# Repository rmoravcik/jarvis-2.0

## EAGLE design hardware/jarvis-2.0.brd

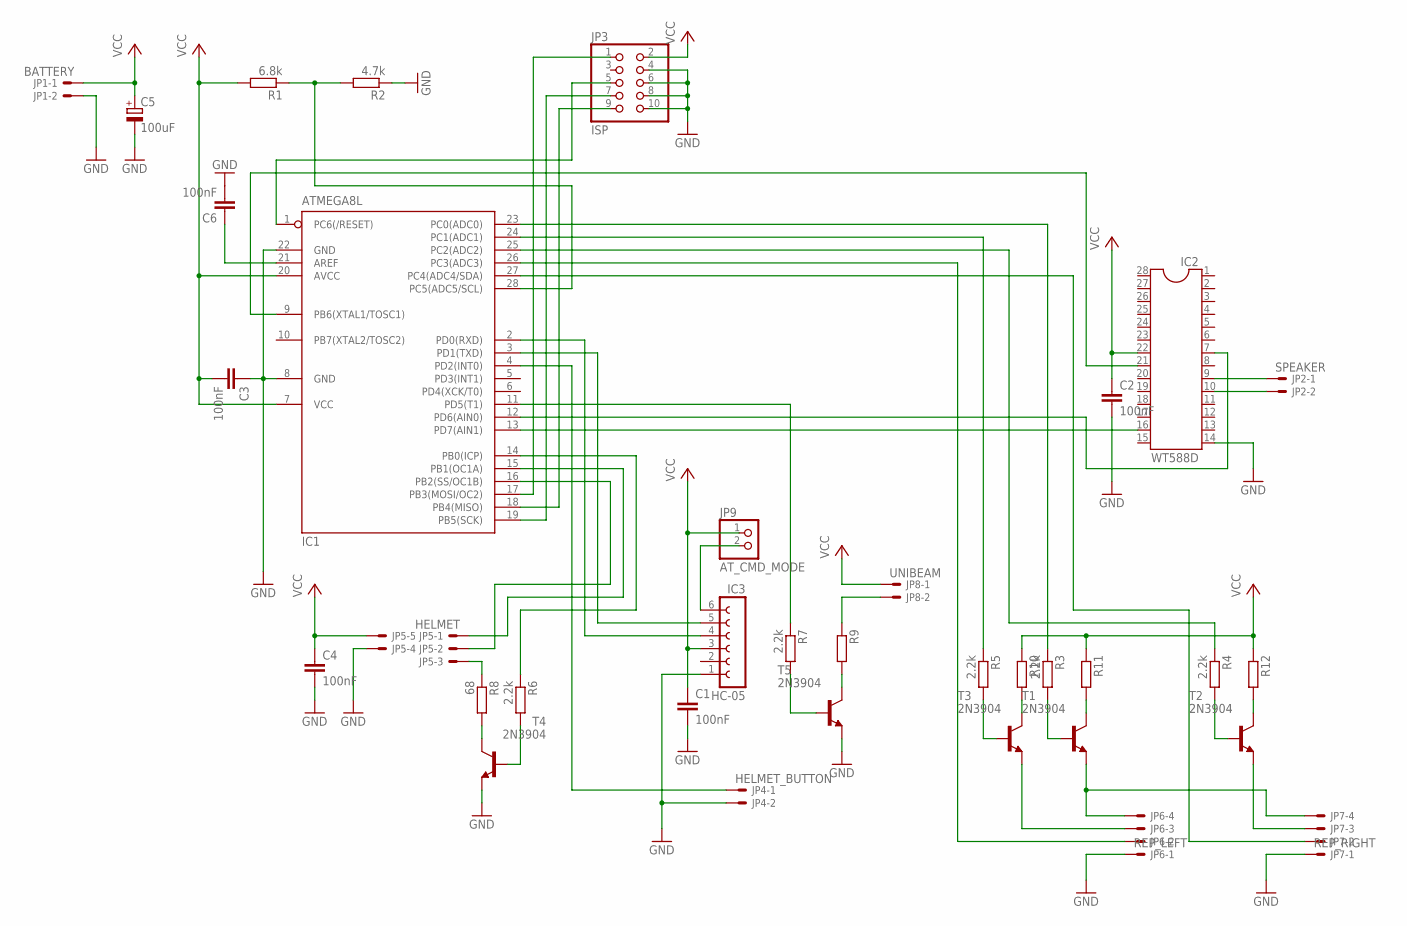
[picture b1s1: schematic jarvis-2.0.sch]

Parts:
C1, C2, C3, C4, C6: 100nF; C2.5-2
C5: 100uF; E5-5
IC1: ATMEGA8L; DIL28-3
IC2: WT588D; DIL28-6
IC3: HC-05; FE06
JP1: BATTERY; 22-23-2021
JP2: SPEAKER; 22-23-2021
JP3: ISP; 2X05
JP4: HELMET_BUTTON; 22-23-2021
JP5: HELMET; 22-23-2051
JP6: REP_LEFT; 22-23-2041
JP7: REP_RIGHT; 22-23-2041
JP8: UNIBEAM; 22-23-2021
JP9: AT_CMD_MODE; 1X02
R1: 6.8k; 0204/7
R2: 4.7k; 0204/7
R3, R4, R5, R6, R7: 2.2k; 0204/7
R8: 68; 0204/7
R9, R10, R11, R12: R-EU_0204/7; 0204/7
T1, T2, T3, T4, T5: 2N3904; TO92-CBE

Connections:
B$1: IC1.14 (PB0(ICP)), R6.1
GND: C1.2, C2.2, C3.1, C4.2, C5.-, C6.2, IC1.8 (GND), IC1.22 (GND), IC2.14, IC3.1, JP1.2, JP3.4, JP3.6, JP3.8, JP3.10, JP4.2, JP5.4, JP6.1, JP7.1, R2.1, T4.E, T5.E
unnamed: IC1.3 (PD1(TXD)), IC3.5
unnamed: IC1.2 (PD0(RXD)), IC3.4
unnamed: IC1.4 (PD2(INT0)), JP4.1
unnamed: IC1.28 (PC5(ADC5/SCL)), R1.1, R2.2
unnamed: IC2.9, JP2.1
unnamed: IC2.10, JP2.2
unnamed: IC1.13 (PD7(AIN1)), IC2.16
unnamed: IC1.9 (PB6(XTAL1/TOSC1)), IC2.21
unnamed: IC1.17 (PB3(MOSI/OC2)), JP3.1
unnamed: IC1.18 (PB4(MISO)), JP3.9
unnamed: IC1.19 (PB5(SCK)), JP3.7
unnamed: IC1.16 (PB2(SS/OC1B)), JP5.2
unnamed: IC1.15 (PB1(OC1A)), JP5.1
unnamed: IC1.11 (PD5(T1)), R7.1
unnamed: IC1.23 (PC0(ADC0)), R3.1
unnamed: R6.2, T4.B
unnamed: JP8.2, R9.1
unnamed: R3.2, T1.B
unnamed: R7.2, T5.B
unnamed: R4.2, T2.B
unnamed: IC1.12 (PD6(AIN0)), IC2.7
unnamed: IC1.24 (PC1(ADC1)), R5.1
unnamed: R5.2, T3.B
unnamed: IC1.25 (PC2(ADC2)), R4.1
unnamed: JP6.4, JP7.4, T1.E
unnamed: JP6.3, T3.E
unnamed: JP7.3, T2.E
unnamed: IC1.26 (PC3(ADC3)), JP6.2
unnamed: IC1.27 (PC4(ADC4/SDA)), JP7.2
unnamed: JP5.3, R8.1
unnamed: R8.2, T4.C
unnamed: R9.2, T5.C
unnamed: R12.2, T2.C
unnamed: R11.2, T1.C
unnamed: R10.2, T3.C
unnamed: C6.1, IC1.21 (AREF)
unnamed: IC3.6, JP9.2
unnamed: IC1.1 (PC6(/RESET)), JP3.5
VCC: C1.1, C2.1, C3.2, C4.1, C5.+, IC1.7 (VCC), IC1.20 (AVCC), IC2.22, IC3.3, JP1.1, JP3.2, JP5.5, JP8.1, JP9.1, R1.2, R10.1, R11.1, R12.1

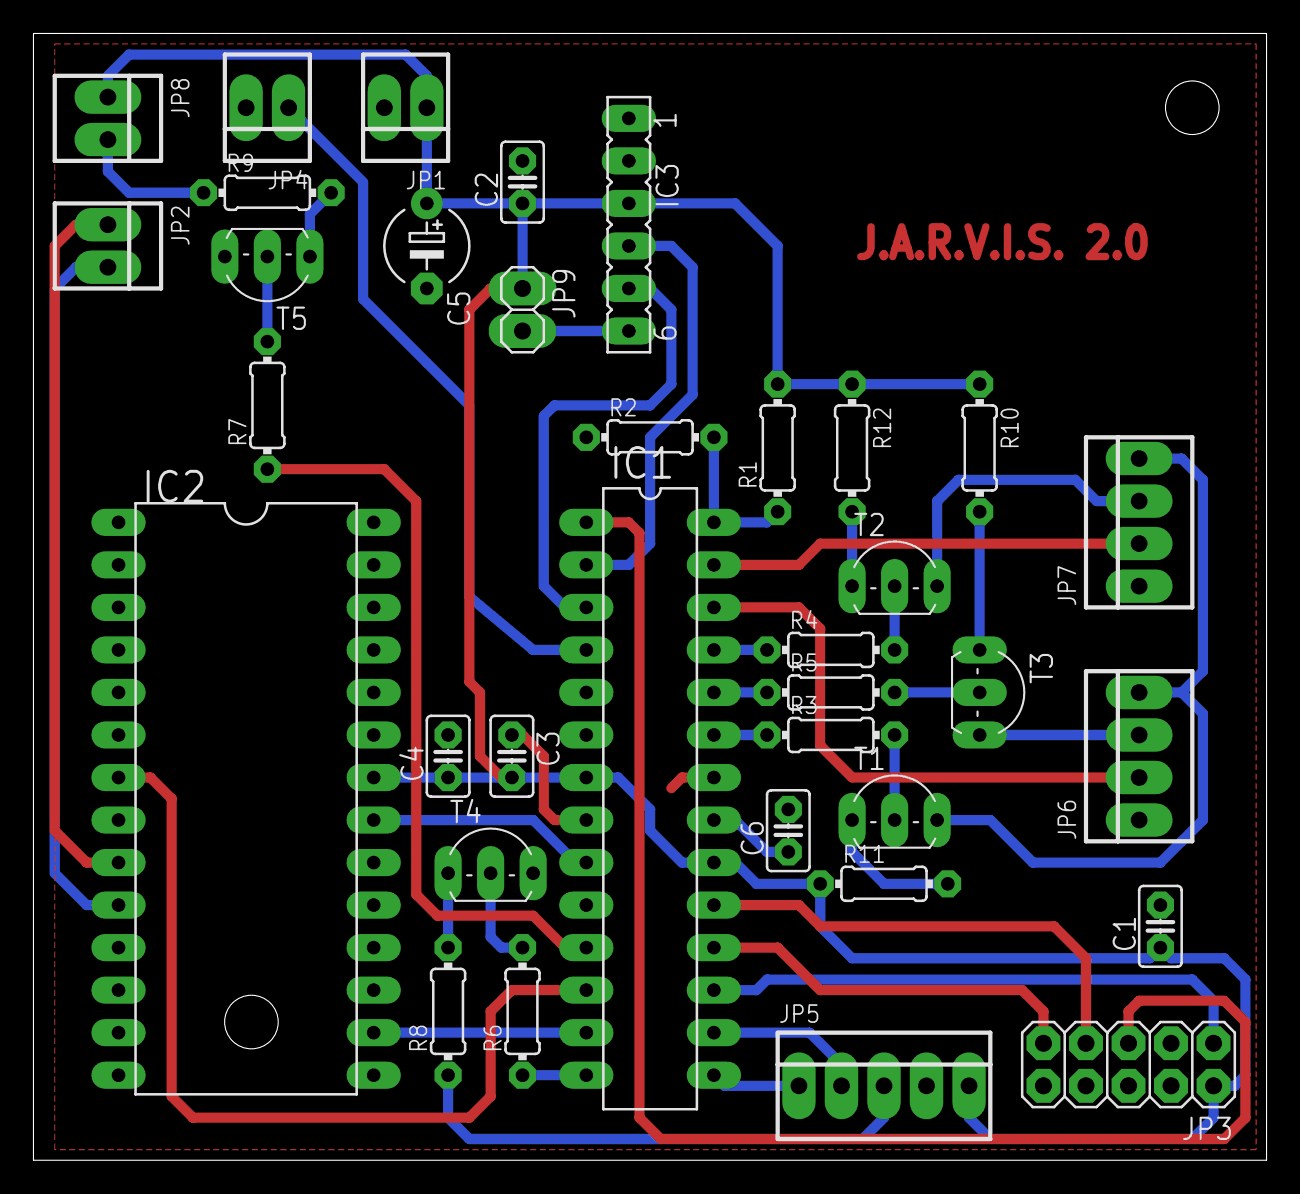
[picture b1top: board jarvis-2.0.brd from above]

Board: 2 copper layers, 73.6 x 67.3 mm, 35 parts (0 on the bottom side), 41 nets.

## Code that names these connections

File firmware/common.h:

/*
 *  jarvis-2.0
 *  Copyright (C) 2014 Roman Moravcik
 *
 *  This program is free software; you can redistribute it and/or modify
 *  it under the terms of the GNU General Public License as published by
 *  the Free Software Foundation; either version 2 of the License, or
 *  (at your option) any later version.
 *
 *  This program is distributed in the hope that it will be useful,
 *  but WITHOUT ANY WARRANTY; without even the implied warranty of
 *  MERCHANTABILITY or FITNESS FOR A PARTICULAR PURPOSE.  See the
 *  GNU General Public License for more details.
 *
 *  You should have received a copy of the GNU General Public License
 *  along with this program; if not, write to the Free Software
 *  Foundation, Inc., 59 Temple Place, Suite 330, Boston, MA  02111-1307  USA
 */

#ifndef COMMON_H
#define COMMON_H

#include <avr/io.h>

#define TRUE				1
#define FALSE				0

#define GPIO_EYES			PB0
#define GPIO_SERVO1			PB1
#define GPIO_SERVO2			PB2
#define GPIO_WT588_BUSY			PB6

#define GPIO_REPULSORS_PWR		PC0
#define GPIO_REPULSOR_LEFT		PC1
#define GPIO_REPULSOR_RIGHT		PC2
#define GPIO_REPULSOR_BUTTON_LEFT	PC3
#define GPIO_REPULSOR_BUTTON_RIGHT	PC4
#define GPIO_BATTERY_SENSE		PC5

#define GPIO_HC05_RXD			PD0
#define GPIO_HC05_TXD			PD1
#define GPIO_FUNC_BUTTON		PD2
#define GPIO_UNIBEAM			PD5
#define GPIO_WT588_RESET		PD6
#define GPIO_WT588_DATA			PD7

#endif // COMMON_H

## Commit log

2014-07-30 Import from iron-man-helmet-controller
2014-07-30 Renamed to jarvis-2.0
2014-07-30 Added wt588d project.
2014-07-30 Removed WT588D Reset pin
2014-07-30 Fixed project name in header
2014-07-30 Code updated to latest HW version.
2014-07-30 Disabled reset
2014-07-31 Tune battery capacity measure
2014-07-31 Changes to follow latest wt588d bin.
2014-08-03 Added ACDC sound
2014-08-03 Added custom random generator
2014-08-04 Fixed random generator. Fixed random generator.#
2014-08-06 Initial bluetooth implementation.
2014-08-06 Added quotes.
2014-08-07 Added comments to code.
2014-08-07 Fixed value of eyes leds resitor.
2014-08-07 Update code to use internal 8Mhz clock.
2014-08-07 Rewritten HC-05 initialization.
2014-08-07 Added hint to get OSCCAL value.
2014-08-07 Added value of OSCCAL register.
2014-08-07 Try to read response.
2014-08-08 Fixed initialization of HC-05.
2014-08-08 Added interrupt driven UART RX.
2014-08-08 Testing receive code
2014-08-10 Fixed serial communucation.
2014-08-10 Cleanup of code.
2014-08-11 Hardcoded strings moved to strings.h
2014-08-11 eyes, repulsor modules replaced by common power module.
2014-08-11 Added command "VERSION"
2014-08-11 Added repulsor button support.
2014-08-11 Print statistics in human readable formtat
2014-08-11 Replace deprecated GIMSK with GICR register.
2014-08-11 Added simple help, unibeam and repulsor commands
2014-08-11 Cleanup of unused sounds.
2014-08-11 Improved blink effect.
2014-08-11 Replace 1 << x with _BV(x) macro.
2014-08-11 Fix compile warning.
2014-08-12 battery_report_capacity() moved to battery.c
2014-08-12 Removed unnecessary code.
2014-08-12 SOUND_CLOCK_AFTERNOON added to voice_play_random()
2014-08-12 Fixed repulsor button logic.
2014-08-13 Added delay before turning on repulsors.
2014-08-13 Handling of repuslor buttons moved to seperated functions.
2014-08-13 Periodic battery checking.
2014-08-13 Allow stoping of playback of random voice messages.
2014-08-13 Report only battery capacity changes.
2014-08-13 Do no ignore report_high flag.
2014-08-14 WT588D busy signal fixes.
2014-08-14 Tabs replaces by spaces. Fixed new line character at the of help.
2014-08-15 Added fortune command. Uppercase serial input.
2014-08-15 Added battery command.
2014-08-15 BUSY fixes 2.
2014-08-15 Revert previous commit.
2014-08-15 BUSY signal fixes 2.
2014-08-15 BUSY fixes 3.
2014-08-18 Added 'REBOOT' command.
2014-08-18 Do not open helmet after reboot if it was closed before.
2014-08-18 Eyes power management moved to helmet module.
2014-08-18 random function moved to voice module.
2014-08-19 Updated sound enum to the latest wt588d firmware.
2014-08-19 Play sound on helmet openning.
2014-08-19 Added playback of new sounds.
2014-08-19 Minize read/write access to internal EEPROM.
2014-08-19 Variable conf_seed renamed to eeprom_seed.
2014-08-19 Initialize helmet as the last module.
2014-08-19 Play sound without waiting.
2014-08-20 Added function to send strings.
2014-08-20 Add automatically CR+LF to the end of sent string.
2014-08-20 Read MCUCSR in early startup.
2014-08-20 Store voice volume in EEPROM
2014-08-20 Clean up of help.
2014-08-20 Added volume command.
2014-08-20 Use git revision instead of harcoded number.
2014-08-20 Update verasion strings.
2014-08-21 Added function to get volume level.
2014-08-21 Calling command VOLUME will get current volue level.
2014-08-21 Rewritten command HELMET.
2014-08-21 Rewritten command EYES.
2014-08-21 Rewritten command REPULSORS.
2014-08-21 Rewritten command UNIBEAM.
2014-08-21 Rewritten command REPULSOR.
2014-08-21 Rename second value behind command from command to parameter.
2014-08-22 Do not print response on get request.
2014-08-22 Handle backspace key in terminal.
2014-08-25 Added a small delay before "just kidding" sound.
2014-08-25 Do not try to fade out device, if it's already off
2014-08-25 Clear deleted character.
2014-08-25 Report battery change only if it's bigger than 5%.
2014-08-25 Fixed compilation of code.
2014-08-26 Rewritten reporting of battery capacity.
2014-08-26 Turn off devices if battery level is critical.
2014-08-26 Fix compilation warning.
2014-08-26 Replace hardcoded values with defines.
2014-08-26 Power on devices only if we have enought battery capacity
2014-08-26 Fix UNIBEAM command.
2014-08-26 Fix backspace.
2014-08-26 Fixed echo.
2014-08-27 Descreased fade in/out time.
2014-08-27 Timer0 initialization/handling moved to battery module.
2014-08-27 Set gpio, uart and adc interrupts not blocking.
2014-08-27 Experimental SW PWM powered devices.
2014-08-27 Try to fix blinking with SW PWM.
2014-08-27 Inverse blinking should be only for eyes LEDs.
2014-08-27 Blink with all devices only if we are not going to power down device.
2014-08-28 Rename "status" to "enabled"
2014-08-28 Clean up of code. Make some global variables static.
2014-08-28 Added alarm and title sounds.
2014-08-28 Start using title and alarm sound.
2014-08-28 Added logic to be able start/stop battery status reporting.
2014-08-28 Rename adc_offset to offset_error.
2014-08-28 Removed non-sense condition.
2014-08-28 Fix blinking effect, rename 'device' to 'devices'.
2014-08-29 Do not blink everytime capacity is < 30%.
2014-08-29 Improved calculation of battery capacity.
2014-08-29 Fade in/out to/from 50% duty at maximum.
2014-08-29 Added duty setting.
2014-08-29 Rewritten PWM using timer.
2014-08-29 Rewritten repulsor blast function.
2014-08-29 Rewritten timer driver SW PWM.
2014-08-29 Removed unwanted blink before/after fade in/out.
2014-08-29 Do not try open/close if already open/closed.
2014-08-29 Fix compilation error.
2014-08-29 Added INTENSITY command.
2014-08-31 Simplification of SW PWM code.
2014-08-31 Fixed settings of intensity on unibeam and repulsors.
2014-08-31 Improve power_failure function.
2014-09-01 Fixed initial state of helmet after power on reset.
2014-09-01 Remove unused header.
2014-09-01 Eliminate global variable 'intensity'
2014-09-01 Finally fixed power failure function.
2014-09-01 Added storing of intensity to EEPROM.
2014-09-01 Added default initialization code if EEPROM is empty.
2014-09-03 Fix variable name ('device' -> 'devices').
2014-09-03 Added possibility to change intensity for each device.
2014-09-03 Modify INTENSITY command to be able to set intensity for each device.
2014-09-03 Do not try to fade out device, if it's already off.
2014-09-04 Added Meego jarvis project.
2014-09-04 Added bluetooth class.
2014-09-04 Fixed my email address, application name.
2014-09-04 Added simple background image.
2014-09-04 Added signal jarvisConnected.
2014-09-05 Added complete firmware interface.
2014-09-05 Cleanup of UI.
2014-09-08 Implemented reading of battery capacity.
2014-09-08 Added periodic battery refresh timer.
2014-09-08 Added initial handling of EYES request/response.
2014-09-08 Added initial handling of FORTUNE request/response.
2014-09-08 Added initial handling of HELMET request/response.
2014-09-09 Registration of Bluetooth class in QML.
2014-09-09 Added effect after jarvis finish speaking.
2014-09-09 Added deconding of remaining responses.
2014-09-09 Added helmet, system, unibeam and updated background image.
2014-09-09 UI optimalizations.
2014-09-10 Wait 2 sec to start after power on.
2014-09-10 Added command ECHO.
2014-09-10 Command FORTUNE renamed to QUOTE.
2014-09-10 Updated background image, updates to match latest firmware.
2014-09-10 Fixed usage of C++ enums in QML.
2014-09-10 Slow down TX to device.
2014-09-11 Fixed getting of initial configuration on connection.
2014-09-11 REBOOT command doesn't have any response.
2014-09-12 Refactoring on QML.
2014-09-12 Reboot replaced with reactor.
2014-09-12 Added suit_diagnostics images.
2014-10-15 Initial rewrite to android.
2014-10-15 Updated layout and images to fit 800x480 display.
2014-10-15 Updated layout and images to fit 800x480 display (2).
2014-10-16 Added suit diagnostics efects.
2014-10-16 Added connection using service uuid.
2014-10-17 Added read timeout.
2014-10-20 Rewritten send/receiving to socket.
2014-10-20 Read volume and intesity on connection.
2014-10-20 FIRMWARE: - Added possiblity to interrupt 'quote' command from bluetooth - Added better initializtion of volume variable
2014-10-20 FIRMWARE: - rename 'size' to 'len'
2014-10-21 CLIENT: - do not start timer on no request messages - put rebooting to log on reboot command
2014-10-22 FIRMWARE: - better indication of voice playing.
2014-10-23 CLIENT: - stop battery update timer on socket error.
2014-10-23 Added click effect.
2014-10-24 CLIENT: - added 2 other pages.
2014-10-24 CLIENT: - refactoring of code.
2014-10-27 CLIENT: - added configuration dialog.
2014-10-27 CLIENT: - added custom font.
2014-10-29 CLIENT: - remove default battery text - do not update value on draging slider - splited mouse area of configuration dialog
2014-10-29 CLIENT: - fixed slider initialization.
2016-05-08 Fix application with Android 6.0. Do not open helmet on power on.
